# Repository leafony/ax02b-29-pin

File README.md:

# AX02B 29-pin Leaf

AX02B 29-pin Leafは、Leafony Busの29ピンを2.54mmピッチのスルーホールパッドへ引き出す変換リーフです。ブレッドボード、ユニバーサル基板、ジャンパワイヤ、ピンヘッダを使った試作や信号確認に利用できます。

## 外観

| Top | Bottom |
| --- | --- |
|  |  |

## 特徴

- Leafony Busの29ピンを2.54mmピッチのスルーホールパッドに変換
- Leafony規格の20mm角リーフ形状

## ピン配置

表面シルクの番号は、左上から下方向に5ピンずつ進む配置です。

| 列 | ピン |
| --- | --- |
| 1 | 1, 2, 3, 4, 5 |
| 2 | 6, 7, 8, 9, 10 |
| 3 | 11, 12, 13, 14, 15 |
| 4 | 16, 17, 18, 19, 20 |
| 5 | 21, 22, 23, 24, 25 |
| 6 | 26, 27, 28, 29 |

KiCad回路図上ではLeafony Busの `F1` から `F29` を各スルーホールパッドへ接続しています。

## ファイル構成

```text
.
├── docs/
│   ├── top.png
│   └── bottom.png
└── kicad/ax02-29-pin/
    ├── ax02-29-pin.kicad_pro
    ├── ax02-29-pin.kicad_sch
    ├── ax02-29-pin.kicad_pcb
    └── panelized/
```

## 製造データ

面付け済みデータは `kicad/ax02-29-pin/panelized/Gerber/` にあります。

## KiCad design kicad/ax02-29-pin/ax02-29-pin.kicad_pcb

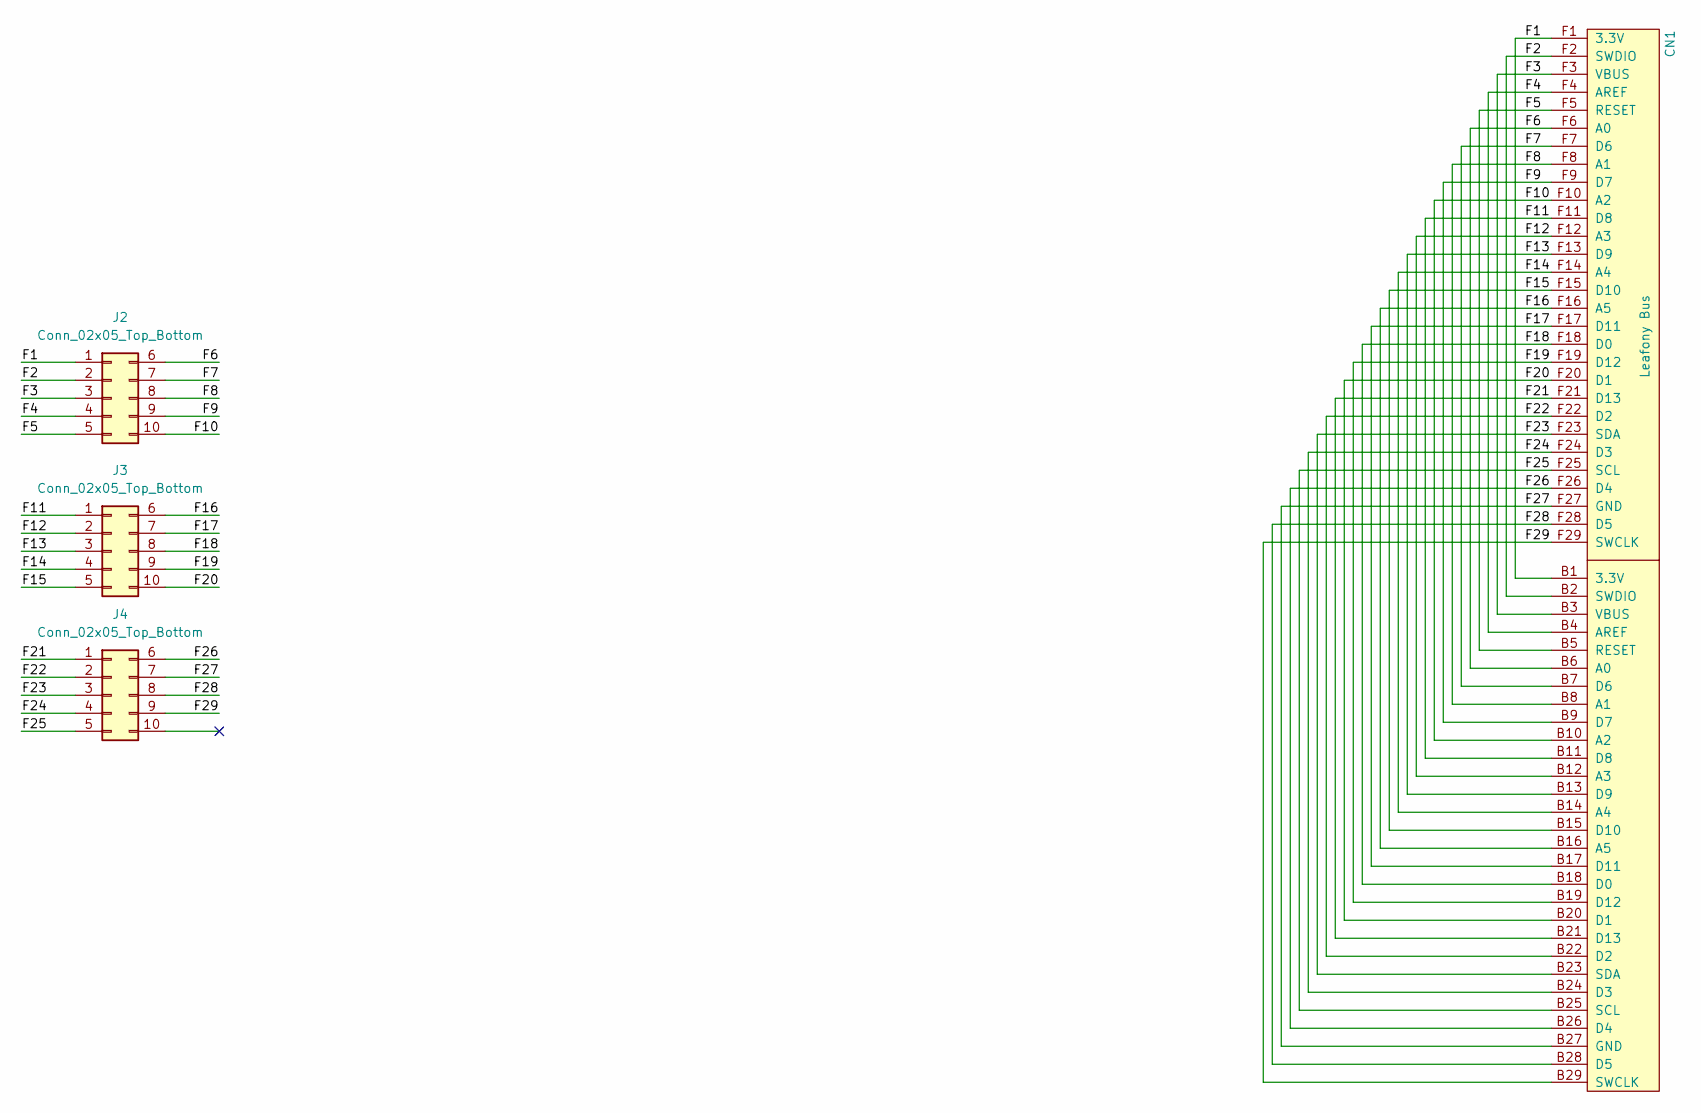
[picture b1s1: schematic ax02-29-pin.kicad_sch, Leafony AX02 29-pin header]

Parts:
CN1: Leafony Bus; CN_F29_B29
J2, J3, J4: Conn_02x05_Top_Bottom; PinHeader_2x05_2.54mm

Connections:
/F1: CN1.B1 (3.3V), CN1.F1 (3.3V), J2.1
/F2: CN1.B2 (SWDIO), CN1.F2 (SWDIO), J2.2
/F3: CN1.B3 (VBUS), CN1.F3 (VBUS), J2.3
/F4: CN1.B4 (AREF), CN1.F4 (AREF), J2.4
/F5: CN1.B5 (RESET), CN1.F5 (RESET), J2.5
/F6: CN1.B6 (A0), CN1.F6 (A0), J2.6
/F7: CN1.B7 (D6), CN1.F7 (D6), J2.7
/F8: CN1.B8 (A1), CN1.F8 (A1), J2.8
/F9: CN1.B9 (D7), CN1.F9 (D7), J2.9
/F10: CN1.B10 (A2), CN1.F10 (A2), J2.10
/F11: CN1.B11 (D8), CN1.F11 (D8), J3.1
/F12: CN1.B12 (A3), CN1.F12 (A3), J3.2
/F13: CN1.B13 (D9), CN1.F13 (D9), J3.3
/F14: CN1.B14 (A4), CN1.F14 (A4), J3.4
/F15: CN1.B15 (D10), CN1.F15 (D10), J3.5
/F16: CN1.B16 (A5), CN1.F16 (A5), J3.6
/F17: CN1.B17 (D11), CN1.F17 (D11), J3.7
/F18: CN1.B18 (D0), CN1.F18 (D0), J3.8
/F19: CN1.B19 (D12), CN1.F19 (D12), J3.9
/F20: CN1.B20 (D1), CN1.F20 (D1), J3.10
/F21: CN1.B21 (D13), CN1.F21 (D13), J4.1
/F22: CN1.B22 (D2), CN1.F22 (D2), J4.2
/F23: CN1.B23 (SDA), CN1.F23 (SDA), J4.3
/F24: CN1.B24 (D3), CN1.F24 (D3), J4.4
/F25: CN1.B25 (SCL), CN1.F25 (SCL), J4.5
/F26: CN1.B26 (D4), CN1.F26 (D4), J4.6
/F27: CN1.B27 (GND), CN1.F27 (GND), J4.7
/F28: CN1.B28 (D5), CN1.F28 (D5), J4.8
/F29: CN1.B29 (SWCLK), CN1.F29 (SWCLK), J4.9

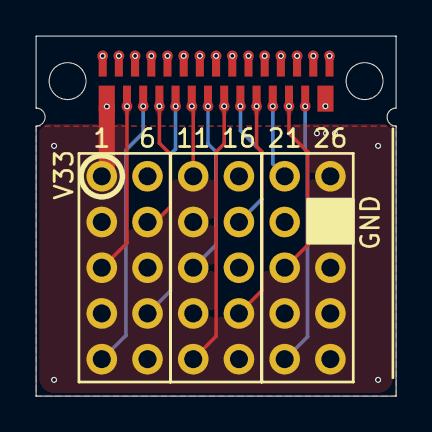
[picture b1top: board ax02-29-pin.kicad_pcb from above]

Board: 4 copper layers, 20.0 x 20.0 mm, 4 parts (0 on the bottom side), 29 nets.

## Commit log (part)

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2026-05-26 レイアウトを作成
2026-05-26 面付データを作成
2026-06-27 面付方法を変更
2026-06-27 不要なガーバーを削除
